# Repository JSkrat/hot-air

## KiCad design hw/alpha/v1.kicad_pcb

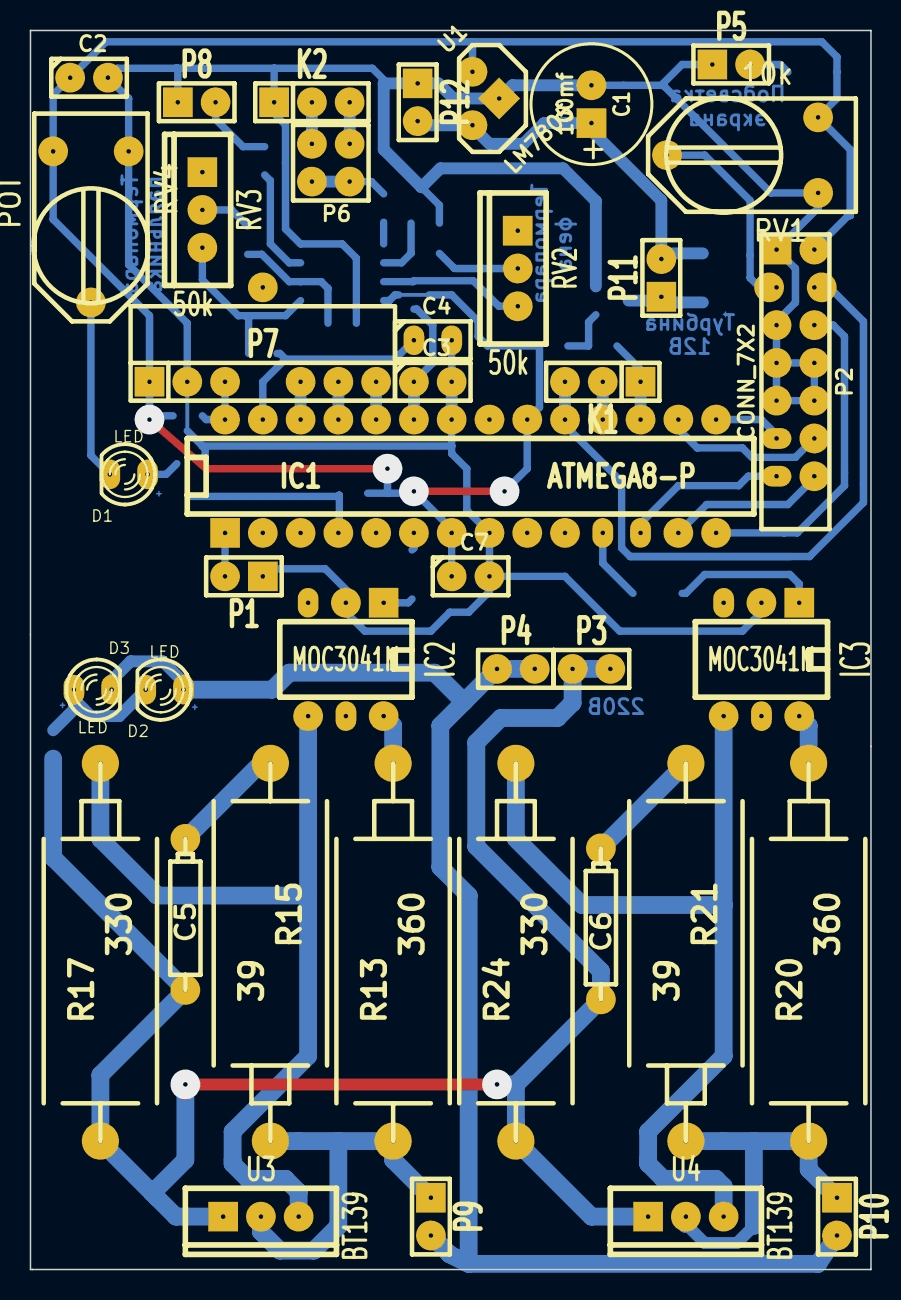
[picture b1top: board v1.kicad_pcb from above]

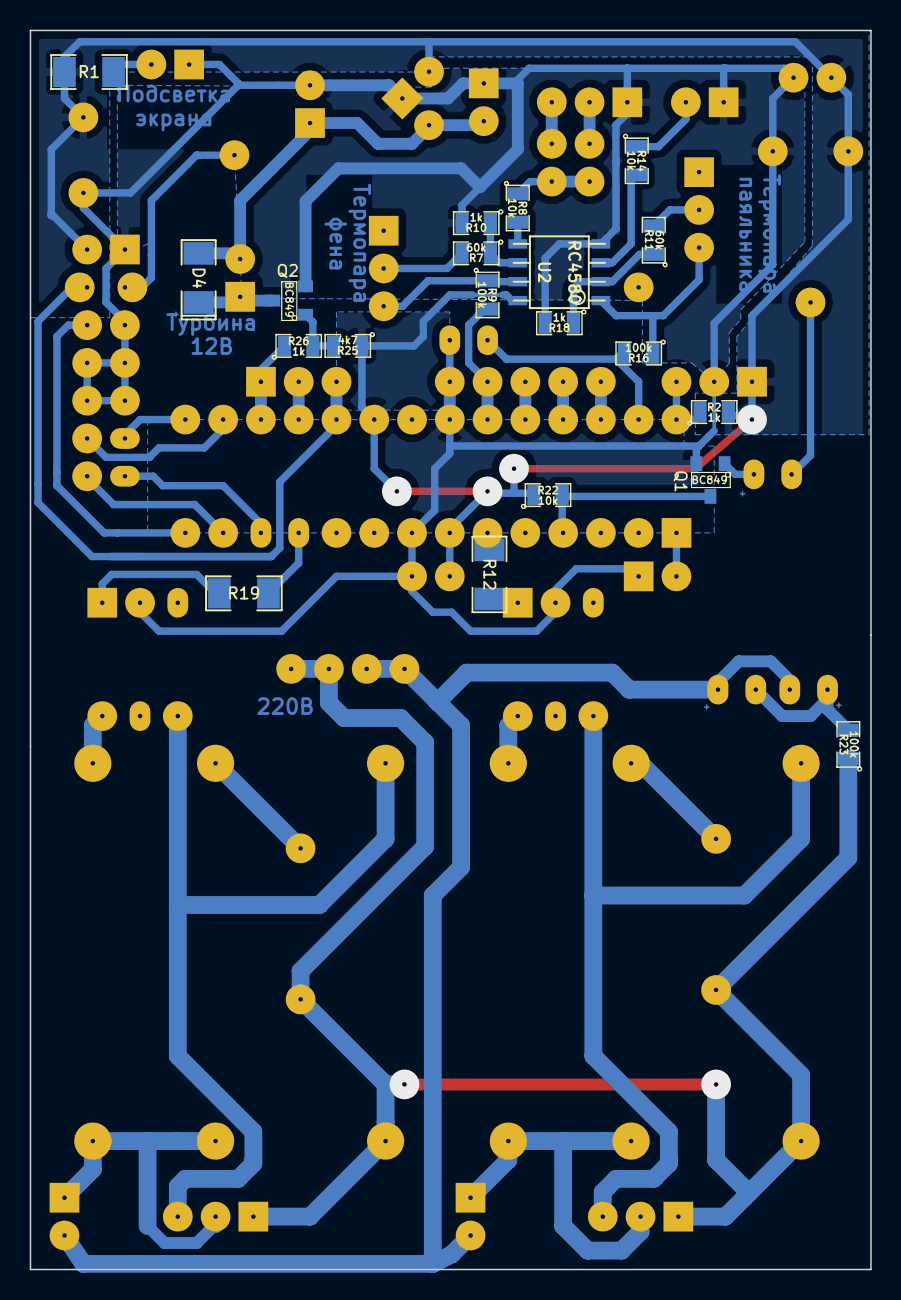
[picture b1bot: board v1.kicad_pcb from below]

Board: 2 copper layers, 56.5 x 83.3 mm, 60 parts (20 on the bottom side), 52 nets.

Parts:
C1: 100mf; C1V8
C2: 1mf; C1
C3, C4, C7: 100n; C1
C5, C6: 0.01; CP4
D1, D2, D3: LED; LED-3MM
D4: DIODE; SM1206POL
IC1: ATMEGA8-P; DIP-28__300
IC2, IC3: MOC3041M; DIP-6__300
K1, K2: CONN_3; SIL-3
P1, P3, P4, P5, P8, P9, P10, P11, P12: CONN_2; SIL-2
P2: CONN_7X2; pin_array_8x2
P6: CONN_2X2; PIN_ARRAY_2X2
P7: CONN_7; SIL-7
Q1, Q2: BC849; SOT23
R1, R12, R19: 300; SM1206
R2, R10, R18, R26: 1k; SM0805
R7, R11: 60k; SM0805
R8, R14, R22: 10k; SM0805
R9, R16, R23: 100k; SM0805
R13, R20: 360; CP10
R15, R21: 39; CP10
R17, R24: 330; CP10
R25: 4k7; SM0805
RV1: 10k; RV2X4
RV2, RV3: 50k; TO220_VERT
RV4: POT; RV2X4
U1: LM7805; LM78LXX
U2: RC4580; so-8
U3, U4: BT139; TO220_VERT

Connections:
+12V: C1.1, D4.2, P11.2, P12.2, U1.VI
/220_NULL: D2.1, D3.2, P4.1, P4.2, P9.2, P10.2
/220_PHASE: C5.2, C6.2, P3.1, P3.2, R17.2, R23.1, R24.2, U3.1, U4.1
/LCD_D4: IC1.15, P2.11
/LCD_D5: IC1.16, P2.12
/LCD_D6: IC1.12, P2.13
/LCD_D7: IC1.13, P2.14
/LCD_E: IC1.14, P2.6
/LCD_RS: IC1.19, K1.3, P2.4
/Phase_sync: IC1.4, Q1.3, R22.2
/buttons: IC1.28, P7.3, R2.1
/pump: IC1.17, K1.1, R26.1
/pump_heat: IC1.11, R19.1
/pump_sens: C3.1, IC1.23, R9.2
/solder: IC1.6, R12.1
/solder_sens: C4.1, IC1.27, R16.2
/var_pump: IC1.25, P7.6
/var_pump_heat: IC1.26, P7.5
/var_solder: IC1.24, P7.7
GND: C1.2, C2.2, C3.2, C4.2, C7.2, IC1.8, IC1.22, IC2.2, IC3.2, K2.1, P1.1, P2.1, P2.5, P2.7, P2.8, P2.9, P2.10, P5.1, P7.2, P8.1, P12.1, Q1.2, Q2.2, R10.2, R18.2, RV1.1, RV4.1, U1.GND, U2.4
unnamed: IC2.1, R12.2
unnamed: Q2.1, R25.2, R26.2
unnamed: IC2.6, R13.1
unnamed: IC2.4, R17.1, U3.3
unnamed: P9.1, R13.2, R15.1, U3.2
unnamed: C5.1, R15.2
unnamed: D1.2, RV4.2
unnamed: R7.1, R10.1, U2.6
unnamed: R9.1, RV2.2, U2.7
unnamed: D1.1, Q1.1
unnamed: D4.1, P11.1, Q2.3
unnamed: IC1.18, K1.2
unnamed: C6.1, R21.2
unnamed: P10.1, R20.2, R21.1, U4.2
unnamed: IC3.1, R19.2
unnamed: R7.2, RV2.3
unnamed: IC3.4, R24.1, U4.3
unnamed: IC3.6, R20.1
unnamed: IC1.1, P1.2
unnamed: P6.2, P6.4, R8.1
unnamed: K2.3, P6.1
unnamed: K2.2, P6.3
unnamed: P5.2, R1.2
unnamed: R11.1, R18.1, U2.2
unnamed: R16.1, RV3.2, U2.1
unnamed: R11.2, RV3.3
unnamed: P8.2, R14.1
unnamed: R14.2, U2.3
unnamed: R8.2, U2.5
unnamed: P2.3, RV1.2
unnamed: D2.2, D3.1, R23.2
VDD: C2.1, C7.1, IC1.7, IC1.20, P2.2, P7.1, R1.1, R2.2, R22.1, R25.1, RV1.3, RV4.3, U1.VO, U2.8

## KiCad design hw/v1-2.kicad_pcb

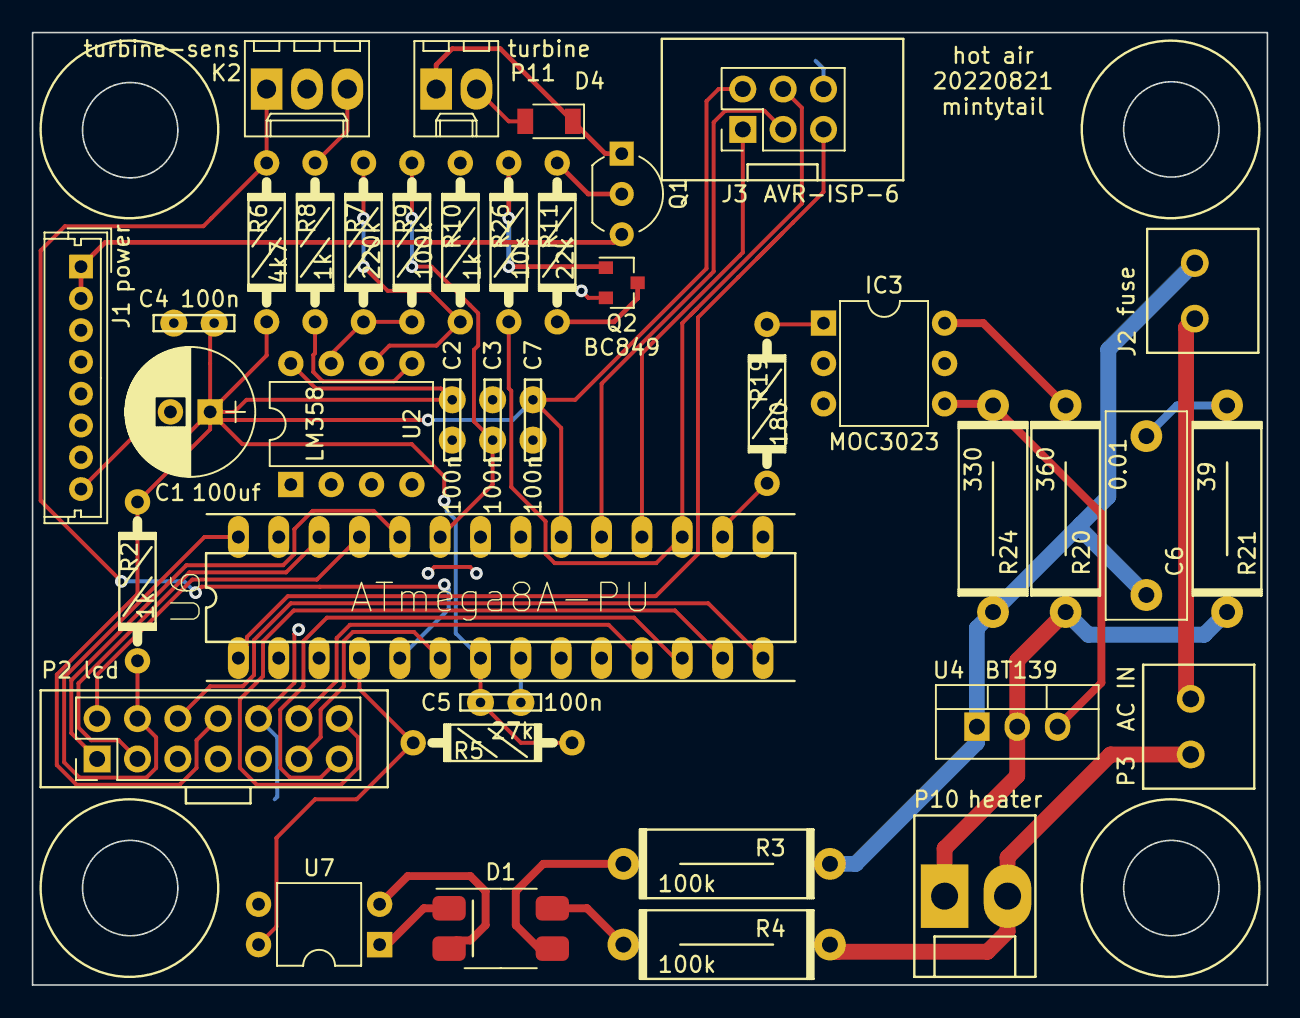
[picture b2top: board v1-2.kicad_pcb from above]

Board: 2 copper layers, 77.7 x 59.9 mm, 39 parts (0 on the bottom side), 40 nets.

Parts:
C1: 100uf; CP_Radial_D8.0mm_P2.50mm
C2, C3, C4, C5, C7: 100n; CC-ceramic_5
C6: 0.01; C_Rect_L13.0mm_W5.0mm_P10.00mm_FKS3_FKP3_MKS4
D1: D_Bridge_+-AA; MB10S
D4: DIODE; D_1206
IC3: MOC3023; DIP-6_W7.62mm
J1: power; Molex_MicroLatch-53253-0870_08x2.00mm_Straight
J2: fuse; 15EDGVC-3.5_2
J3: AVR-ISP-6; AVR_ISP_TH_6
K2: turbine-sens; Molex_KK-6410-03_03x2.54mm_Straight
P2: lcd; Pin_Header_Straight_2x07_Pitch2.54mm_bare
P3: AC IN; 15EDGVC-3.5_2
P10: heater; Molex_KK-41791-02_02x3.96mm_Straight
P11: turbine; Molex_KK-6410-02_02x2.54mm_Straight
Q1: KT209; TO-92_Inline_Wide
Q2: BC849; SOT-23
R2, R8, R10: 1k; R1-MLT_0.125_10
R3, R4: 100k; R1-MLT_0.5_13
R5: 27k; R1-MLT_0.125_10
R6: 4k7; R1-MLT_0.125_10
R7: 220k; R1-MLT_0.125_10
R9: 100k; R1-MLT_0.125_10
R11: 22k; R1-MLT_0.125_10
R19: 180; R1-MLT_0.125_10
R20: 360; R1-MLT_0.5_13
R21: 39; R1-MLT_0.5_13
R24: 330; R1-MLT_0.5_13
R26: 10k; R1-MLT_0.125_10
U2: LM358; DIP-8_W7.62mm
U4: BT139; TO-220-3_Vertical
U6: ATmega8A-PU; atmega8-DIL28-3_panel
U7: EL817; DIP-4_W7.62mm

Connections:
/220_NULL: P3.1, P10.2, R4.2
/220_PHASE: C6.2, J2.2, R3.2, R24.2, U4.1
/+5: C1.1, C2.1, C4.1, C5.1, C7.1, J1.8, J3.2, P2.8, R2.1, R5.1, R6.1, U2.8, U6.7, U6.20
/+42: J1.1, J1.2, Q1.3
/LCD_CLK: P2.14, U6.13
/LCD_CS: P2.12, U6.11
/LCD_PWR: P2.6, U6.14
/LCD_RST: P2.11, U6.6
/LCD_SDA: P2.13, U6.12
/buttons: P2.4, R2.2, U6.28
/gnd: C1.2, C2.2, C3.2, C4.2, C5.2, C7.2, D4.2, IC3.2, J1.3, J1.4, J1.5, J1.6, J1.7, J3.6, K2.2, P2.10, P11.2, Q2.2, R10.2, U2.2, U2.3, U2.4, U6.8, U6.22, U7.3
/idle: K2.1, R6.2, U6.5
/phase_sync: R5.2, U6.4, U7.4
/prog-miso: J3.1, U6.18
/prog-mosi: J3.4, R26.1, U6.17
/prog-sck: J3.3, U6.19
/pump_heat: R19.1, U6.16
/pump_sens: C3.1, R9.2, U6.23
/reset: J3.5, U6.1
/var_pump: P2.2, U6.25
/var_pump_heat: P2.3, U6.26
/var_solder: P2.1, U6.24
unnamed: C6.1, R21.2
unnamed: D1.1, U7.1
unnamed: D1.2, U7.2
unnamed: D1.3, R3.1
unnamed: D1.4, R4.1
unnamed: D4.1, P11.1, Q1.1
unnamed: IC3.1, R19.2
unnamed: IC3.4, R24.1, U4.3
unnamed: IC3.6, R20.1
unnamed: J2.1, P3.2
unnamed: K2.3, R8.1
unnamed: P10.1, R20.2, R21.1, U4.2
unnamed: Q1.2, R11.1
unnamed: Q2.1, R26.2
unnamed: Q2.3, R11.2
unnamed: R7.2, R9.1, U2.7
unnamed: R8.2, U2.5
unnamed: R7.1, R10.1, U2.6

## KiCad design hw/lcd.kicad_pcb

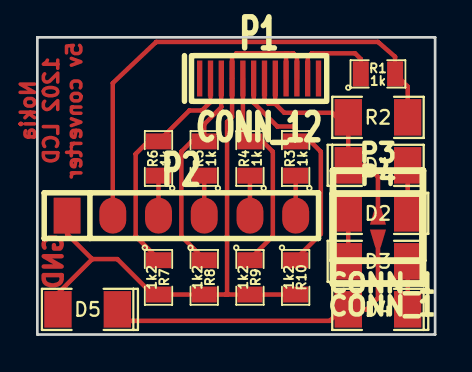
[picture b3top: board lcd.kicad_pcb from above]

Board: 2 copper layers, 22.1 x 16.5 mm, 19 parts (0 on the bottom side), 16 nets.

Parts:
D1, D2, D3, D4, D5: DIODE; SM1206POL
P1: CONN_12; SIL-12
P2: CONN_6; SIL-6
P3, P4: CONN_1; 1PIN_SMD
R1, R3, R4, R5, R6: 1k; SM0805
R2: 220; SM1206
R7, R8, R9, R10: 1k2; SM0805

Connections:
/gnd: D5.2, P1.4, P1.9, P1.10, P2.1, R7.2, R8.2, R9.2, R10.2
/vcc: P2.2, R1.2, R2.2
unnamed: P1.5, R4.2, R9.1
unnamed: P1.6, R3.2, R10.1
unnamed: P1.3, R5.2, R8.1
unnamed: P1.2, R6.2, R7.1
unnamed: D4.2, D5.1, P4.1
unnamed: D1.1, P1.7, P1.8, P3.1, R2.1
unnamed: D3.2, D4.1
unnamed: D2.2, D3.1
unnamed: D1.2, D2.1
unnamed: P1.11, R1.1
unnamed: P2.6, R3.1
unnamed: P2.5, R4.1
unnamed: P2.4, R5.1
unnamed: P2.3, R6.1

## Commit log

2025-03-15 update fw for new pcb
